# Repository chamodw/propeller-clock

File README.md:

# propeller-clock
A simple propeller clock project using an ATMEGA328p and 16 Leds

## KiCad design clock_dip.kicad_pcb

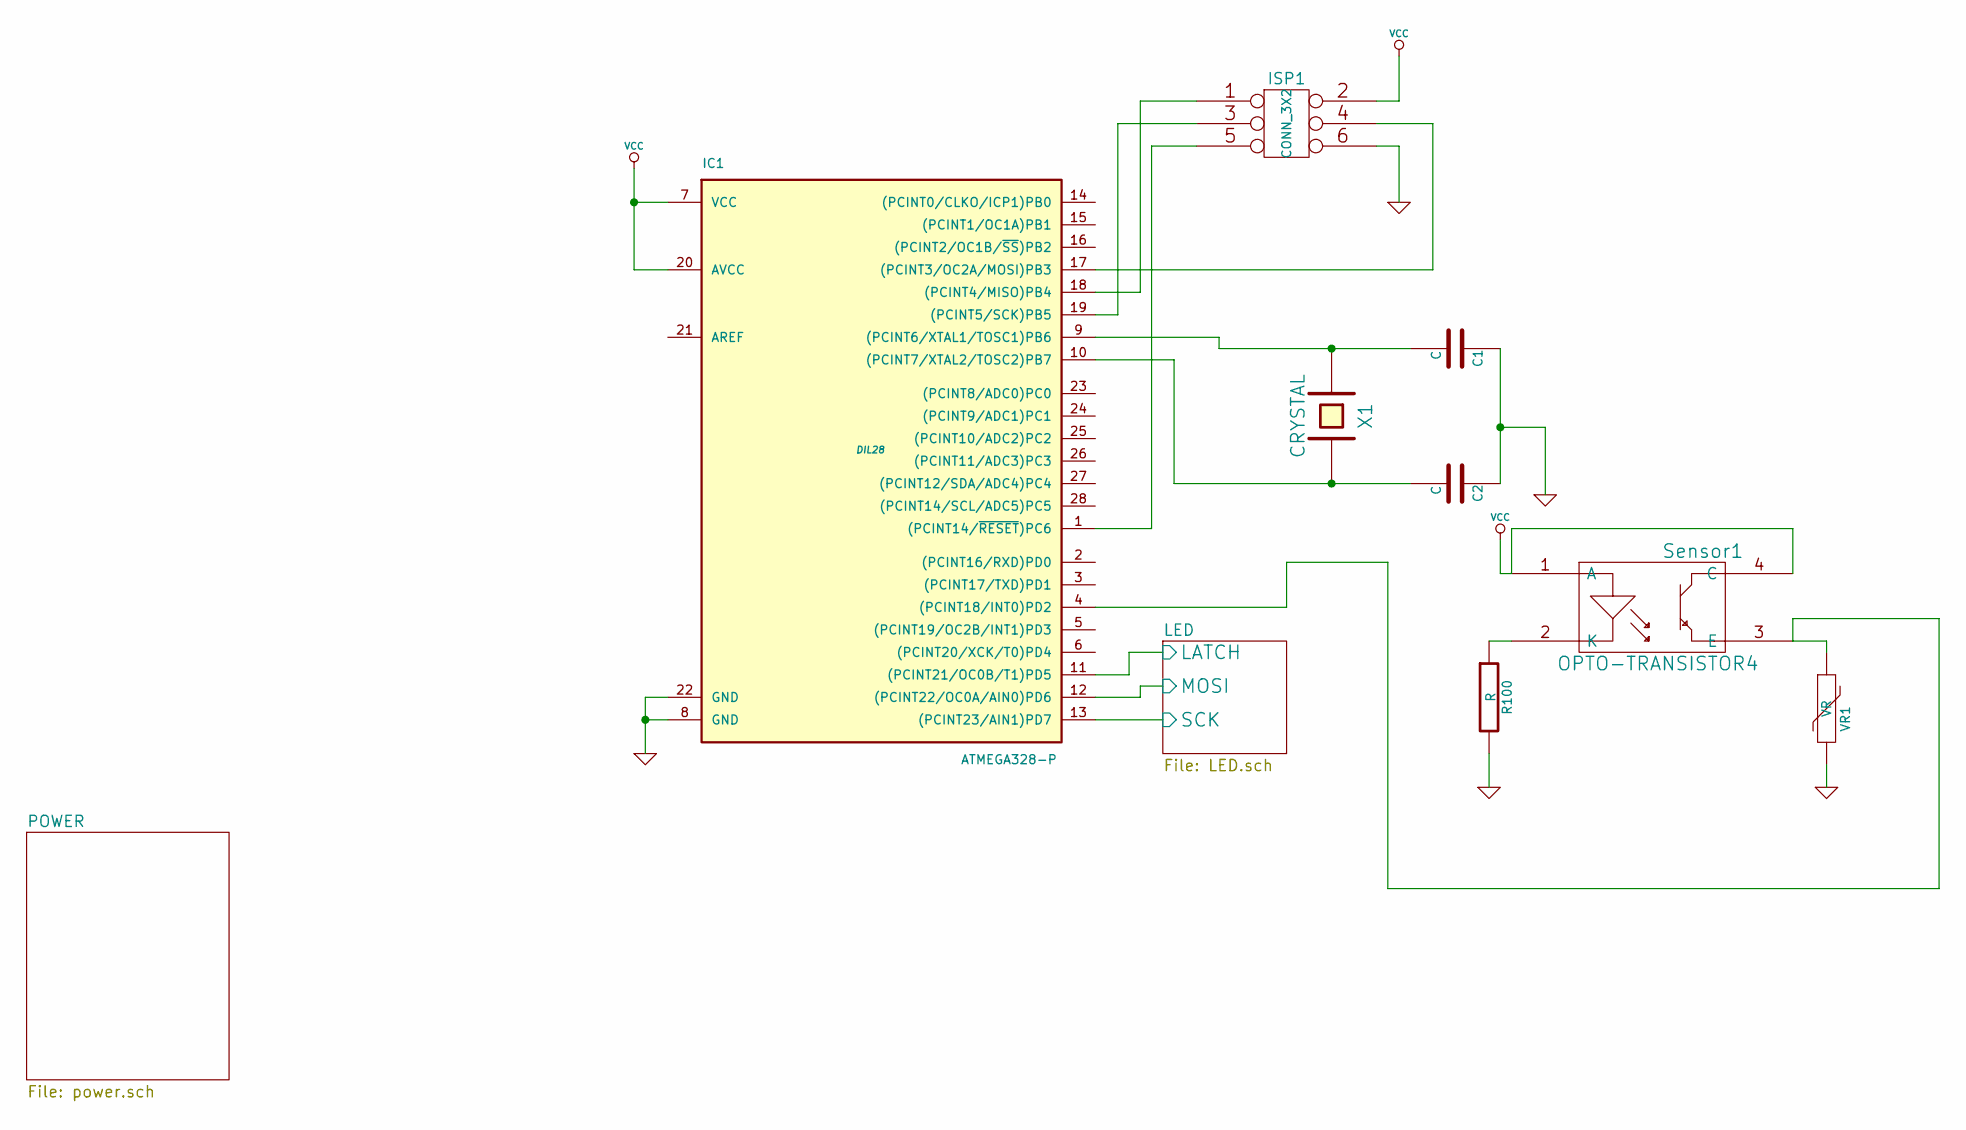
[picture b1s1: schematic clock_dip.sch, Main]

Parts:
C1, C2: C
IC1: ATMEGA328-P; DIL28
ISP1: CONN_3X2
R100: R
Sensor1: OPTO-TRANSISTOR4
VR1: VR
X1: CRYSTAL

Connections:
/LED/LATCH: IC1.11 ((PCINT21/OC0B/T1)PD5); also elsewhere on the board
/LED/MOSI: IC1.12 ((PCINT22/OC0A/AIN0)PD6); also elsewhere on the board
/LED/SCK: IC1.13 ((PCINT23/AIN1)PD7); also elsewhere on the board
GND: C1.1, C2.1, IC1.8 (GND), IC1.22 (GND), ISP1.6, R100.2, VR1.2; also elsewhere on the board
unnamed: C1.2, IC1.9 ((PCINT6/XTAL1/TOSC1)PB6), X1.1
unnamed: C2.2, IC1.10 ((PCINT7/XTAL2/TOSC2)PB7), X1.2
unnamed: IC1.1 ((PCINT14/~RESET~)PC6), ISP1.5
unnamed: IC1.4 ((PCINT18/INT0)PD2), Sensor1.3 (E), VR1.1
unnamed: IC1.17 ((PCINT3/OC2A/MOSI)PB3), ISP1.4
unnamed: IC1.18 ((PCINT4/MISO)PB4), ISP1.1
unnamed: IC1.19 ((PCINT5/SCK)PB5), ISP1.3
unnamed: R100.1, Sensor1.2 (K)
VCC: IC1.7 (VCC), IC1.20 (AVCC), ISP1.2, Sensor1.1 (A), Sensor1.4 (C); also elsewhere on the board

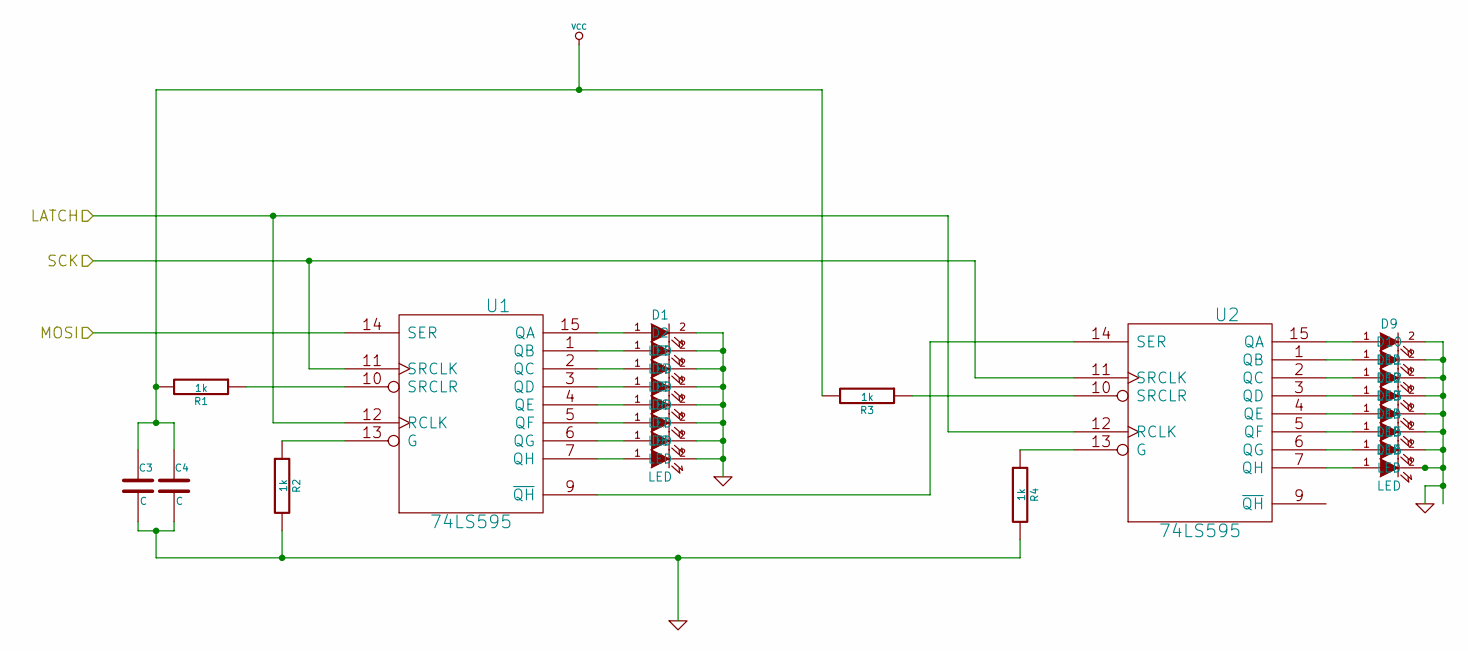
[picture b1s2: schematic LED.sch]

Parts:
C3, C4: C
D1, D2, D3, D4, D5, D6, D7, D8, D9, D10, D11, D12, D13, D14, D15, D16: LED
R1, R2, R3, R4: 1k
U1, U2: 74LS595

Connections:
/LED/LATCH: U1.12 (RCLK), U2.12 (RCLK); also elsewhere on the board
/LED/MOSI: U1.14 (SER); also elsewhere on the board
/LED/SCK: U1.11 (SRCLK), U2.11 (SRCLK); also elsewhere on the board
GND: C3.2, C4.2, D1.2 (K), D2.2 (K), D3.2 (K), D4.2 (K), D5.2 (K), D6.2 (K), D7.2 (K), D8.2 (K), D9.2 (K), D10.2 (K), D11.2 (K), D12.2 (K), D13.2 (K), D14.2 (K), D15.2 (K), D16.2 (K), R2.2, R4.2, U1.8 (GND), U2.8 (GND); also elsewhere on the board
unnamed: D1.1 (A), U1.15 (QA)
unnamed: D2.1 (A), U1.1 (QB)
unnamed: D3.1 (A), U1.2 (QC)
unnamed: D4.1 (A), U1.3 (QD)
unnamed: D5.1 (A), U1.4 (QE)
unnamed: D6.1 (A), U1.5 (QF)
unnamed: D7.1 (A), U1.6 (QG)
unnamed: D8.1 (A), U1.7 (QH)
unnamed: D9.1 (A), U2.15 (QA)
unnamed: D10.1 (A), U2.1 (QB)
unnamed: D11.1 (A), U2.2 (QC)
unnamed: D12.1 (A), U2.3 (QD)
unnamed: D13.1 (A), U2.4 (QE)
unnamed: D14.1 (A), U2.5 (QF)
unnamed: D15.1 (A), U2.6 (QG)
unnamed: D16.1 (A), U2.7 (QH)
unnamed: R1.1, U1.10 (SRCLR)
unnamed: R2.1, U1.13 (G)
unnamed: R3.1, U2.10 (SRCLR)
unnamed: R4.1, U2.13 (G)
unnamed: U1.9 (~QH), U2.14 (SER)
VCC: C3.1, C4.1, R1.2, R3.2, U1.16 (VCC), U2.16 (VCC); also elsewhere on the board

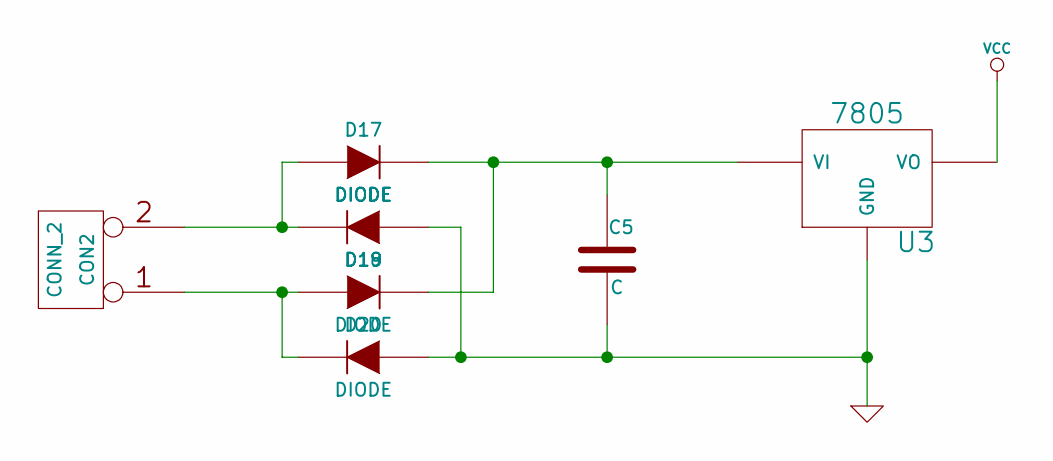
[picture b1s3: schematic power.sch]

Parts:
C5: C
CON2: CONN_2
D17, D18, D19, D20: DIODE
U3: 7805

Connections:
GND: C5.2, D18.1 (A), D20.1 (A), U3.GND; also elsewhere on the board
unnamed: C5.1, D17.2 (K), D19.2 (K), U3.VI
unnamed: CON2.1, D19.1 (A), D20.2 (K)
unnamed: CON2.2 (PM), D17.1 (A), D18.2 (K)
VCC: U3.VO; also elsewhere on the board

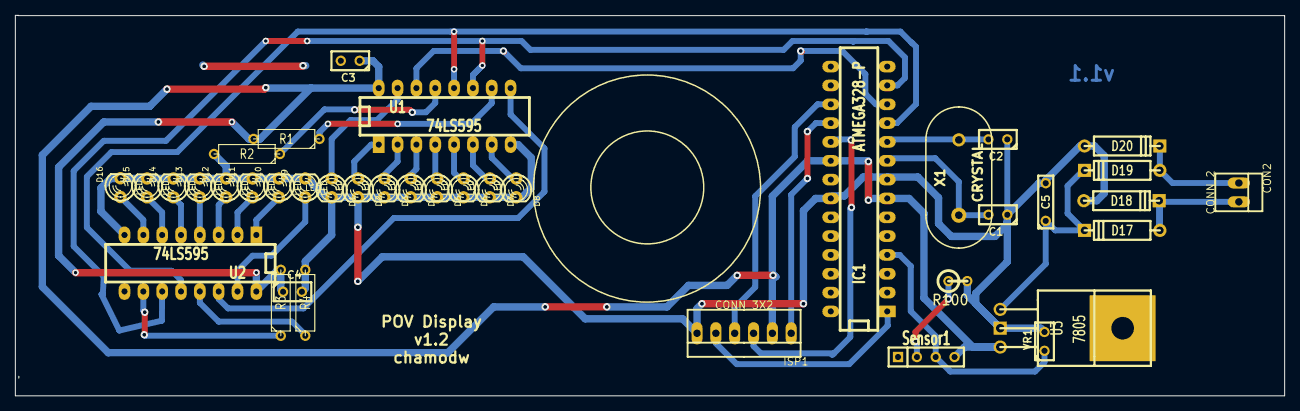
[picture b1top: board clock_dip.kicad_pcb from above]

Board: 2 copper layers, 171.2 x 51.3 mm, 39 parts (0 on the bottom side), 37 nets.

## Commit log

2015-03-28 Added existing files
2015-03-28 Corrected comments on code
